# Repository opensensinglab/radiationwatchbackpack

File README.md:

External signal analysis backpack for the Radiation Watch Type 5 high-energy particle detector
======

Work-in-progress.  Please use at your own risk. <br>

This is a board intended to function as an external comparator for the Radiation Watch Type 5 high energy particle detector.  The stock RWT5 comes with a comparator whose threshold appears very conservative, and it appears that lower-energy particles can be detected by affixing an external comparator such as this.  This project is also working towards including an energy-level detection mechanism. <br>

Earlier versions of this backpack were used for the Open Source Desktop Computed Tomography Scanner (OpenCT, http://www.tricorderproject.org/blog/tag/openct/), and the Arducoder Mini open-source science tricorder-like device ( https://hackaday.io/project/1395-open-source-science-tricorder ). 

# Open Source

This project is open source software and hardware, and is released under various open licenses.

# Disclaimer

**DISCLAIMER OF WARRANTIES AND LIMITATION OF LIABILITY.**

UNLESS OTHERWISE SEPARATELY UNDERTAKEN BY THE LICENSOR, TO THE EXTENT POSSIBLE, THE LICENSOR OFFERS THE LICENSED MATERIAL AS-IS AND AS-AVAILABLE, AND MAKES NO REPRESENTATIONS OR WARRANTIES OF ANY KIND CONCERNING THE LICENSED MATERIAL, WHETHER EXPRESS, IMPLIED, STATUTORY, OR OTHER. THIS INCLUDES, WITHOUT LIMITATION, WARRANTIES OF TITLE, MERCHANTABILITY, FITNESS FOR A PARTICULAR PURPOSE, NON-INFRINGEMENT, ABSENCE OF LATENT OR OTHER DEFECTS, ACCURACY, OR THE PRESENCE OR ABSENCE OF ERRORS, WHETHER OR NOT KNOWN OR DISCOVERABLE. WHERE DISCLAIMERS OF WARRANTIES ARE NOT ALLOWED IN FULL OR IN PART, THIS DISCLAIMER MAY NOT APPLY TO YOU.

TO THE EXTENT POSSIBLE, IN NO EVENT WILL THE LICENSOR BE LIABLE TO YOU ON ANY LEGAL THEORY (INCLUDING, WITHOUT LIMITATION, NEGLIGENCE) OR OTHERWISE FOR ANY DIRECT, SPECIAL, INDIRECT, INCIDENTAL, CONSEQUENTIAL, PUNITIVE, EXEMPLARY, OR OTHER LOSSES, COSTS, EXPENSES, OR DAMAGES ARISING OUT OF THIS PUBLIC LICENSE OR USE OF THE LICENSED MATERIAL, EVEN IF THE LICENSOR HAS BEEN ADVISED OF THE POSSIBILITY OF SUCH LOSSES, COSTS, EXPENSES, OR DAMAGES. WHERE A LIMITATION OF LIABILITY IS NOT ALLOWED IN FULL OR IN PART, THIS LIMITATION MAY NOT APPLY TO YOU.

THE DISCLAIMER OF WARRANTIES AND LIMITATION OF LIABILITY PROVIDED ABOVE SHALL BE INTERPRETED IN A MANNER THAT, TO THE EXTENT POSSIBLE, MOST CLOSELY APPROXIMATES AN ABSOLUTE DISCLAIMER AND WAIVER OF ALL LIABILITY.

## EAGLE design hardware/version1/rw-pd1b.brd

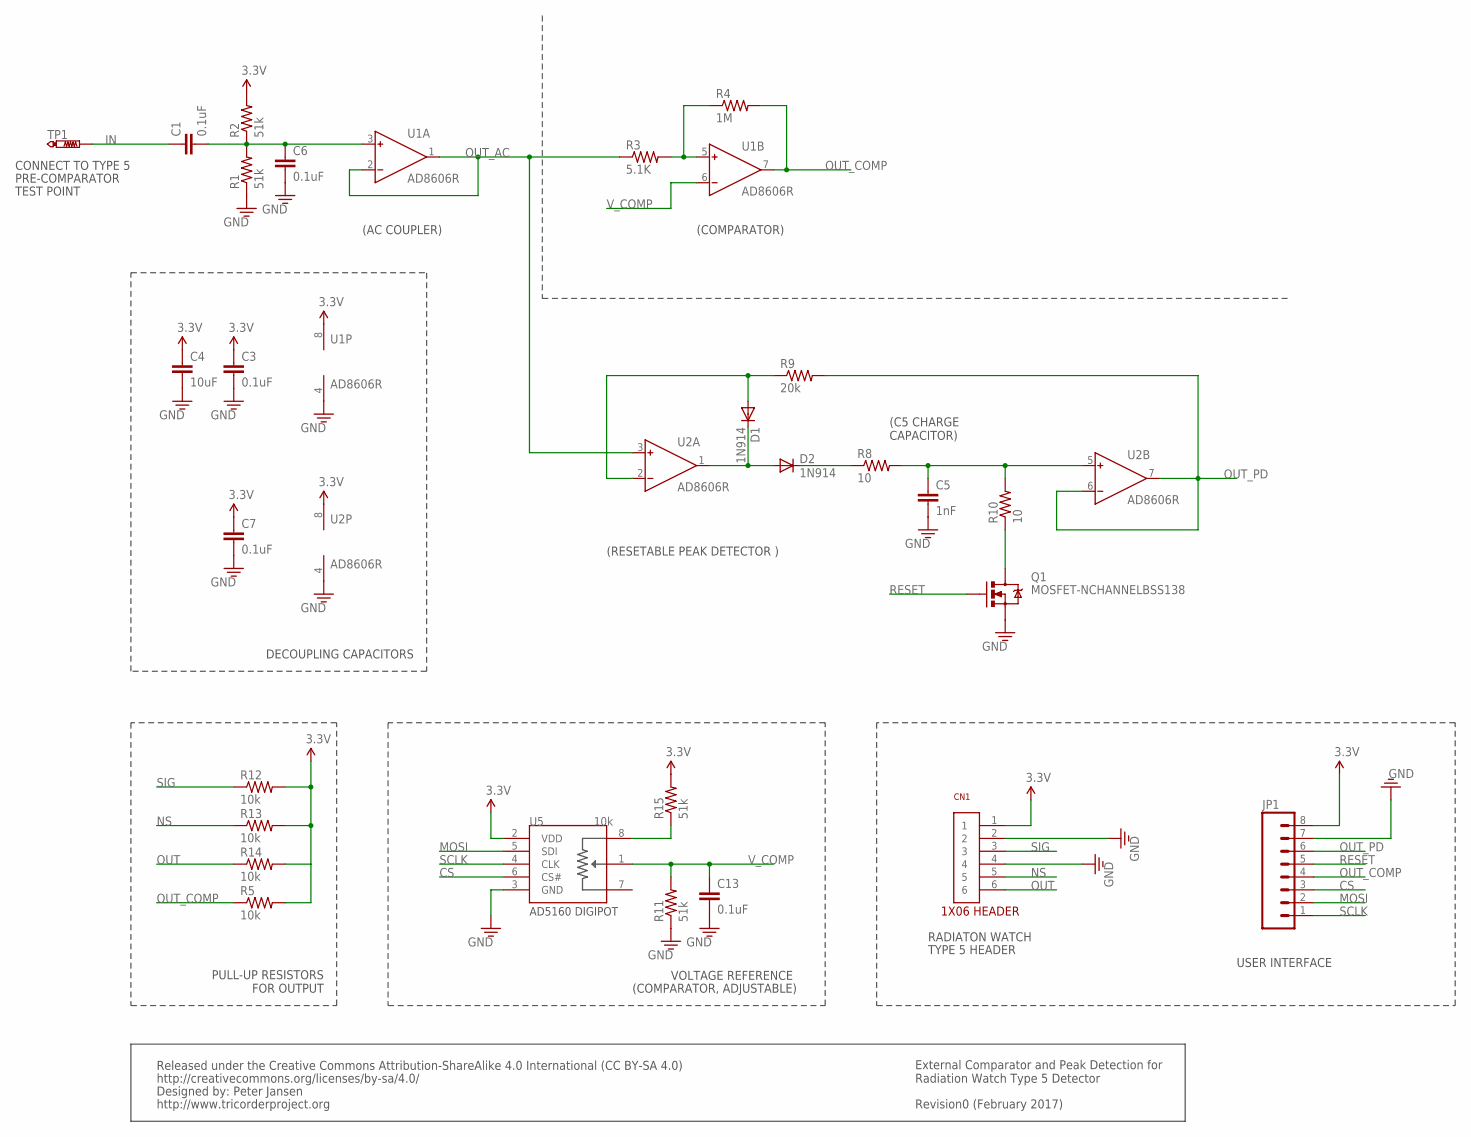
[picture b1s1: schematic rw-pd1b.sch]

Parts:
C1, C3, C6, C7, C13: 0.1uF; 0603
C4: 10uF; 0603
C5: 1nF; 0603
CN1: 1X06
D1, D2: 1N914; SOD-323
JP1: M08LOCK; 1X08_LOCK
Q1: MOSFET-NCHANNELBSS138; SOT23
R1, R2, R11, R15: 51k; 0603
R3: 5.1K; 0603
R4: 1M; 0603
R5, R12, R13, R14: 10k; 0603
R8, R10: 10; 0603
R9: 20k; 0603
TP1: PTR1PAD1-13; P1-13
U1, U2: AD8606R; SO8
U5: 10k; SOT-23-8

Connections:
3.3V: C3.1, C4.1, C7.1, CN1.1, JP1.8, R2.2, R5.2, R12.2, R13.2, R14.2, R15.2, U1.8 (V+), U2.8 (V+), U5.2 (VDD)
CS: JP1.3, U5.6 (CS#)
GND: C3.2, C4.2, C5.2, C6.2, C7.2, C13.2, CN1.2, CN1.4, JP1.7, Q1.2 (S), R1.1, R11.1, U1.4 (V-), U2.4 (V-), U5.3 (GND)
IN: C1.1, TP1.TP
MOSI: JP1.2, U5.5 (SDI)
unnamed: C1.2, C6.1, R1.2, R2.1, U1.3 (IN+)
unnamed: R3.2, R4.1, U1.5 (IN+)
unnamed: D1.A, R9.1, U2.2 (IN-)
unnamed: D1.C, D2.A, U2.1 (OUT)
unnamed: D2.C, R8.1
unnamed: C5.1, R8.2, R10.2, U2.5 (IN+)
unnamed: Q1.3 (D), R10.1
unnamed: R15.1, U5.8 (A)
NS: CN1.5, R13.1
OUT: CN1.6, R14.1
OUT_AC: R3.1, U1.1 (OUT), U1.2 (IN-), U2.3 (IN+)
OUT_COMP: JP1.4, R4.2, R5.1, U1.7 (OUT)
OUT_PD: JP1.6, R9.2, U2.6 (IN-), U2.7 (OUT)
RESET: JP1.5, Q1.1 (G)
SCLK: JP1.1, U5.4 (CLK)
SIG: CN1.3, R12.1
V_COMP: C13.1, R11.2, U1.6 (IN-), U5.1 (W)

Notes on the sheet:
(AC COUPLER)
(COMPARATOR)
CONNECT TO TYPE 5
PRE-COMPARATOR
TEST POINT
RADIATON WATCH
TYPE 5 HEADER
Released under the Creative Commons Attribution-ShareAlike 4.0 International (CC BY-SA 4.0)
http://creativecommons.org/licenses/by-sa/4.0/
Designed by: Peter Jansen
http://www.tricorderproject.org
Revision0 (February 2017)
External Comparator and Peak Detection for Radiation Watch Type 5 Detector
(C5 CHARGE CAPACITOR)
(RESETABLE PEAK DETECTOR )
VOLTAGE REFERENCE
(COMPARATOR, ADJUSTABLE)
PULL-UP RESISTORS FOR OUTPUT
DECOUPLING CAPACITORS
USER INTERFACE

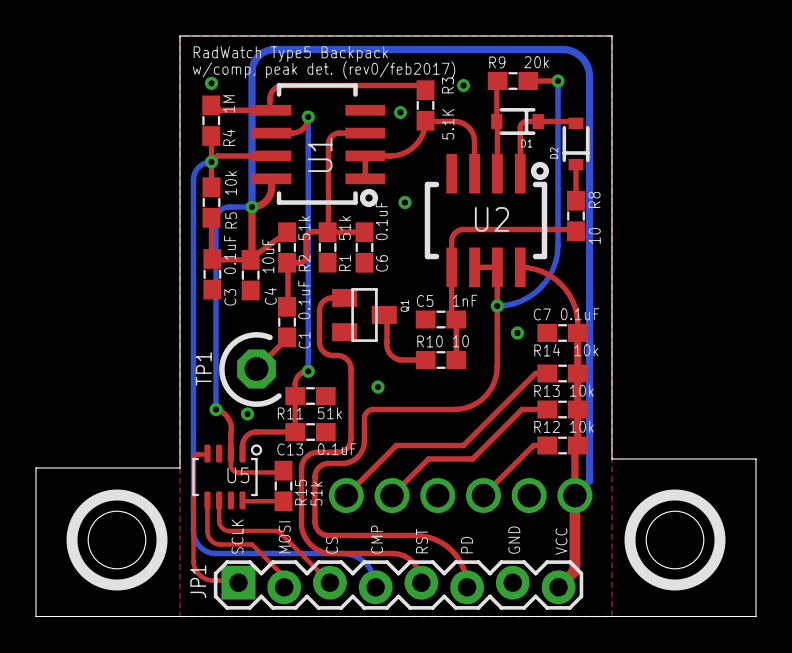
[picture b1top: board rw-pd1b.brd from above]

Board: 2 copper layers, 40.0 x 32.2 mm, 29 parts (1 on the bottom side), 22 nets.

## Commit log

2017-03-07 Initial README
2017-03-07 Added version 1 of new Radiation Watch Type 5 backpack

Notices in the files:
parts and their libraries:
SparkFun-DiscreteSemi: Licensing: Creative Commons ShareAlike 4.0 International - https://creativecommons.org/licenses/by-sa/4.0
